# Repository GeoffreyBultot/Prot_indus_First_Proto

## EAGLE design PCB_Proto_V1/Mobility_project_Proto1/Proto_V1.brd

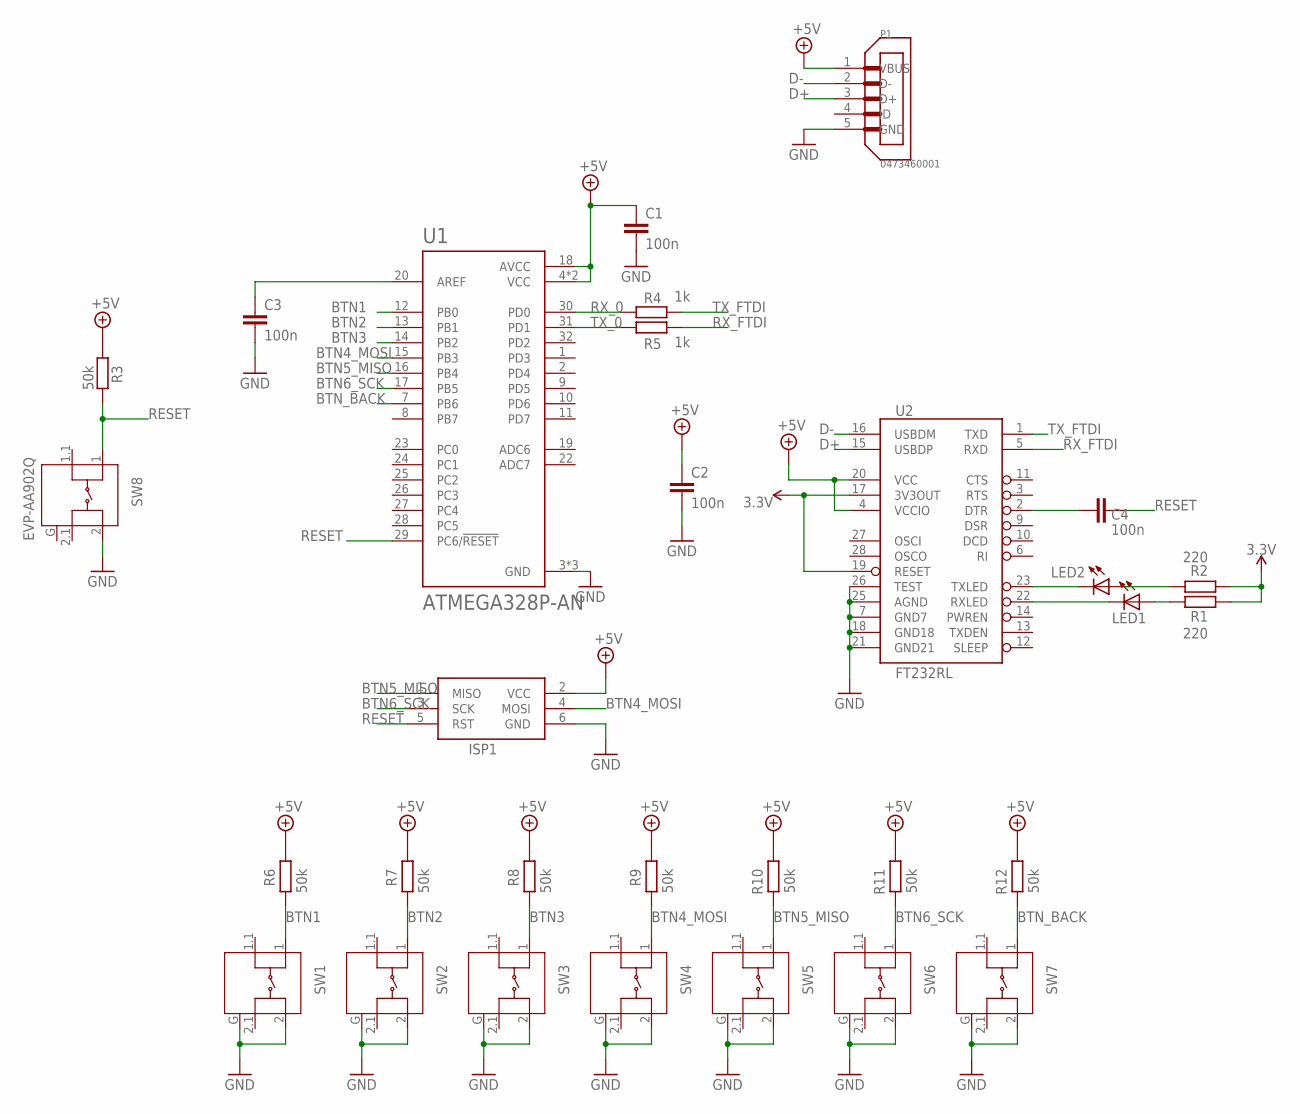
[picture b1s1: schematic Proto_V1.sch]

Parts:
C1, C2, C3, C4: 100n; CAP_0805
ISP1: AVRISP-6; AVRISP
LED1, LED2: LEDCHIP-LED0805; CHIP-LED0805
P1: 0473460001; MOLEX_0473460001
R1, R2: 220; R0805
R3, R6, R7, R8, R9, R10, R11, R12: 50k; R0805
R4, R5: 1k; R0805
SW1, SW2, SW3, SW4, SW5, SW6, SW7, SW8: EVP-AA902Q
U1: ATMEGA328P-AN; QFP80P900X900X120-32N
U2: FT232RL; SSOP28DB

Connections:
3.3V: R1.1, R2.1, U2.17 (3V3OUT), U2.19 (RESET)
+5V: C1.1, C2.1, ISP1.2 (VCC), P1.1 (VBUS), R3.1, R6.1, R7.1, R8.1, R9.1, R10.1, R11.1, R12.1, U1.4 (VCC), U1.6 (VCC), U1.18 (AVCC), U2.4 (VCCIO), U2.20 (VCC)
BTN1: R6.2, SW1.1, U1.12 (PB0)
BTN2: R7.2, SW2.1, U1.13 (PB1)
BTN3: R8.2, SW3.1, U1.14 (PB2)
BTN4_MOSI: ISP1.4 (MOSI), R9.2, SW4.1, U1.15 (PB3)
BTN5_MISO: ISP1.1 (MISO), R10.2, SW5.1, U1.16 (PB4)
BTN6_SCK: ISP1.3 (SCK), R11.2, SW6.1, U1.17 (PB5)
BTN_BACK: R12.2, SW7.1, U1.7 (PB6)
D+: P1.3 (D+), U2.15 (USBDP)
D-: P1.2 (D-), U2.16 (USBDM)
GND: C1.2, C2.2, C3.2, ISP1.6 (GND), P1.5 (GND), SW1.2, SW1.G (SHIELD), SW2.2, SW2.G (SHIELD), SW3.2, SW3.G (SHIELD), SW4.2, SW4.G (SHIELD), SW5.2, SW5.G (SHIELD), SW6.2, SW6.G (SHIELD), SW7.2, SW7.G (SHIELD), SW8.2, U1.3 (GND), U1.5 (GND), U1.21 (GND), U2.7 (GND7), U2.18 (GND18), U2.21 (GND21), U2.25 (AGND), U2.26 (TEST)
unnamed: LED1.A, R1.2
unnamed: LED2.C, U2.23 (TXLED)
unnamed: LED1.C, U2.22 (RXLED)
unnamed: LED2.A, R2.2
unnamed: C4.2, U2.2 (DTR)
unnamed: C3.1, U1.20 (AREF)
RESET: C4.1, ISP1.5 (RST), R3.2, SW8.1, U1.29 (PC6/!RESET)
RX_0: R4.1, U1.30 (PD0)
RX_FTDI: R5.2, U2.5 (RXD)
TX_0: R5.1, U1.31 (PD1)
TX_FTDI: R4.2, U2.1 (TXD)

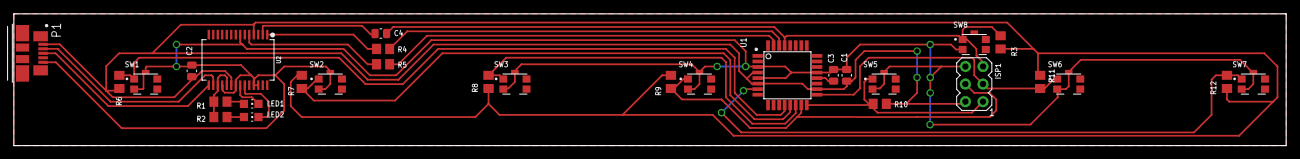
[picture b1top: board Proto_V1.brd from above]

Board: 2 copper layers, 183.8 x 19.0 mm, 30 parts (0 on the bottom side), 23 nets.

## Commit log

2019-12-14 Add arduino code
2019-12-14 Add PCB and schematic
2019-12-15 Ajout PCB et 3D
2019-12-21 Add F3Z files

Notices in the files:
parts and their libraries:
SparkFun-IC-Comms: Licensing: Creative Commons ShareAlike 4.0 International - https://creativecommons.org/licenses/by-sa/4.0
